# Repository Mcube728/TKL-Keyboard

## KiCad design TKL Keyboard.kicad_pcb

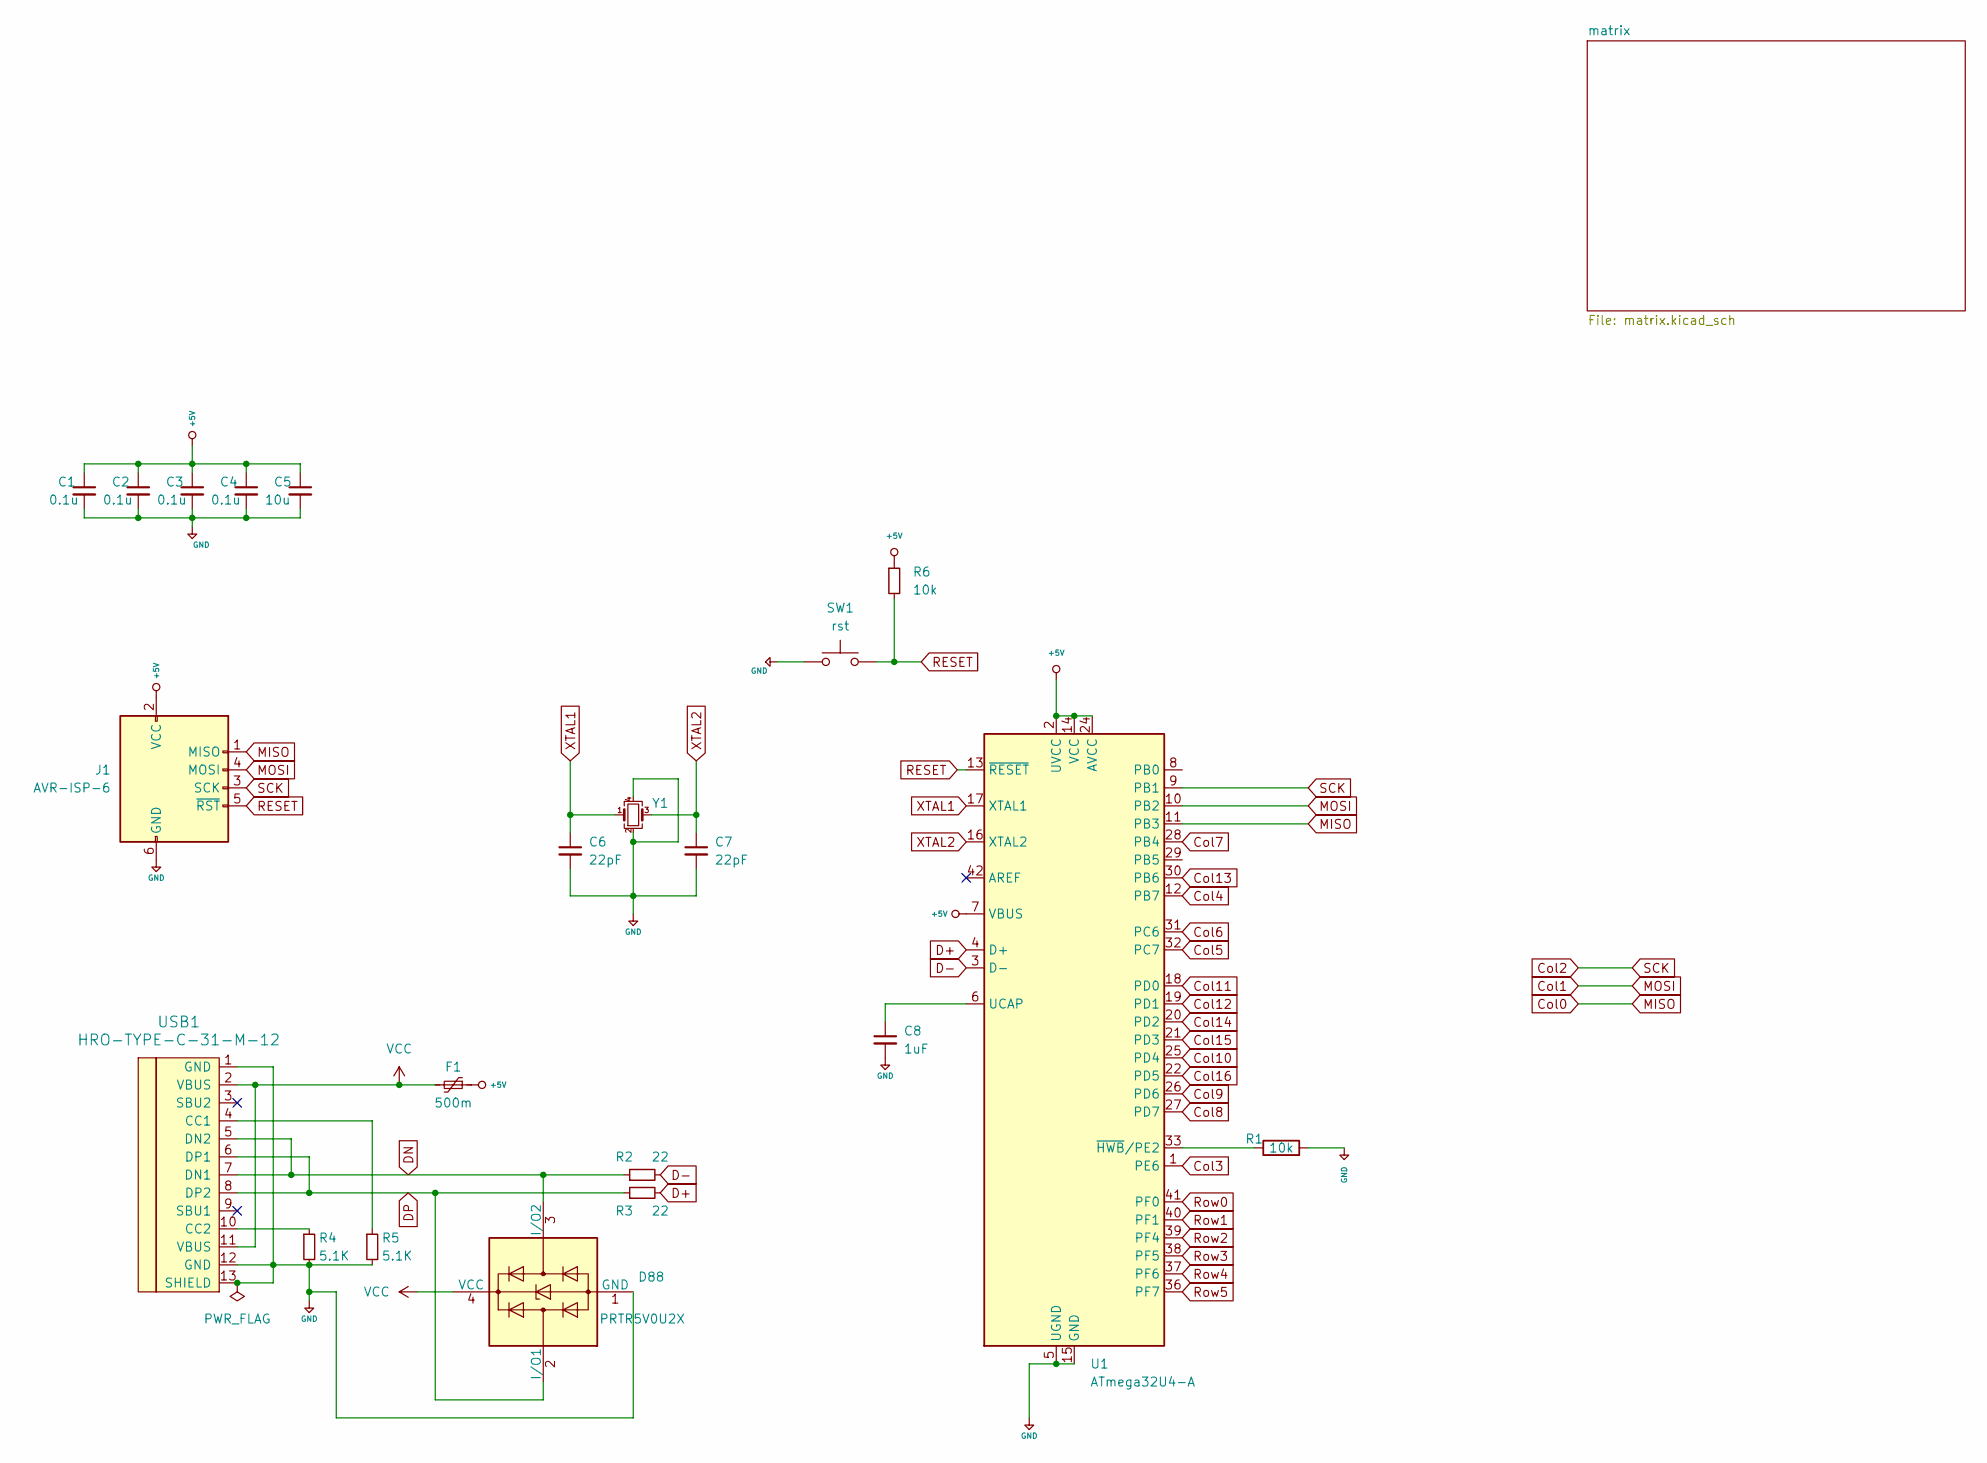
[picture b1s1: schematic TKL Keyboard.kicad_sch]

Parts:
C1, C2, C3, C4: 0.1u; C_0805_2012Metric_Pad1.18x1.45mm_HandSolder
C5: 10u; C_0805_2012Metric_Pad1.18x1.45mm_HandSolder
C6, C7: 22pF; C_0805_2012Metric_Pad1.18x1.45mm_HandSolder
C8: 1uF; C_0805_2012Metric_Pad1.18x1.45mm_HandSolder
D88: PRTR5V0U2X; SOT-143
F1: 500m; Fuse_1206_3216Metric_Pad1.42x1.75mm_HandSolder
J1: AVR-ISP-6; Reset_Pretty-Mask
R1, R6: 10k; R_0805_2012Metric_Pad1.20x1.40mm_HandSolder
R2, R3: 22; R_0805_2012Metric_Pad1.20x1.40mm_HandSolder
R4, R5: 5.1K; R_0805_2012Metric_Pad1.20x1.40mm_HandSolder
SW1: rst; SW_SPST_SKQG_WithStem
U1: ATmega32U4-A; TQFP-44_10x10mm_P0.8mm
USB1: HRO-TYPE-C-31-M-12; HRO-TYPE-C-31-M-12-HandSoldering
Y1: Crystal_SMD_3225-4Pin_3.2x2.5mm_HandSoldering

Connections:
Col0: J1.1 (MISO), U1.11 (PB3); also elsewhere on the board
Col1: J1.4 (MOSI), U1.10 (PB2); also elsewhere on the board
Col2: J1.3 (SCK), U1.9 (PB1); also elsewhere on the board
Col3: U1.1 (PE6); also elsewhere on the board
Col4: U1.12 (PB7); also elsewhere on the board
Col5: U1.32 (PC7); also elsewhere on the board
Col6: U1.31 (PC6); also elsewhere on the board
Col7: U1.28 (PB4); also elsewhere on the board
Col8: U1.27 (PD7); also elsewhere on the board
Col9: U1.26 (PD6); also elsewhere on the board
Col10: U1.25 (PD4); also elsewhere on the board
Col11: U1.18 (PD0); also elsewhere on the board
Col12: U1.19 (PD1); also elsewhere on the board
Col13: U1.30 (PB6); also elsewhere on the board
Col14: U1.20 (PD2); also elsewhere on the board
Col15: U1.21 (PD3); also elsewhere on the board
Col16: U1.22 (PD5); also elsewhere on the board
D+: R3.2, U1.4 (D+)
D-: R2.2, U1.3 (D-)
DN: D88.3 (I/O2), R2.1, USB1.5 (DN2), USB1.7 (DN1)
DP: D88.2 (I/O1), R3.1, USB1.6 (DP1), USB1.8 (DP2)
unnamed: C8.1, U1.6 (UCAP)
unnamed: R1.1, U1.33 (~HWB/PE2)
unnamed: R5.1, USB1.4 (CC1)
unnamed: R4.1, USB1.10 (CC2)
RESET: J1.5 (~RST), R6.2, SW1.2, U1.13 (~RESET)
Row0: U1.41 (PF0); also elsewhere on the board
Row1: U1.40 (PF1); also elsewhere on the board
Row2: U1.39 (PF4); also elsewhere on the board
Row3: U1.38 (PF5); also elsewhere on the board
Row4: U1.37 (PF6); also elsewhere on the board
Row5: U1.36 (PF7); also elsewhere on the board
VCC: D88.4 (VCC), F1.2, USB1.2 (VBUS), USB1.11 (VBUS)
XTAL1: C6.1, U1.17 (XTAL1), Y1.1
XTAL2: C7.1, U1.16 (XTAL2), Y1.3

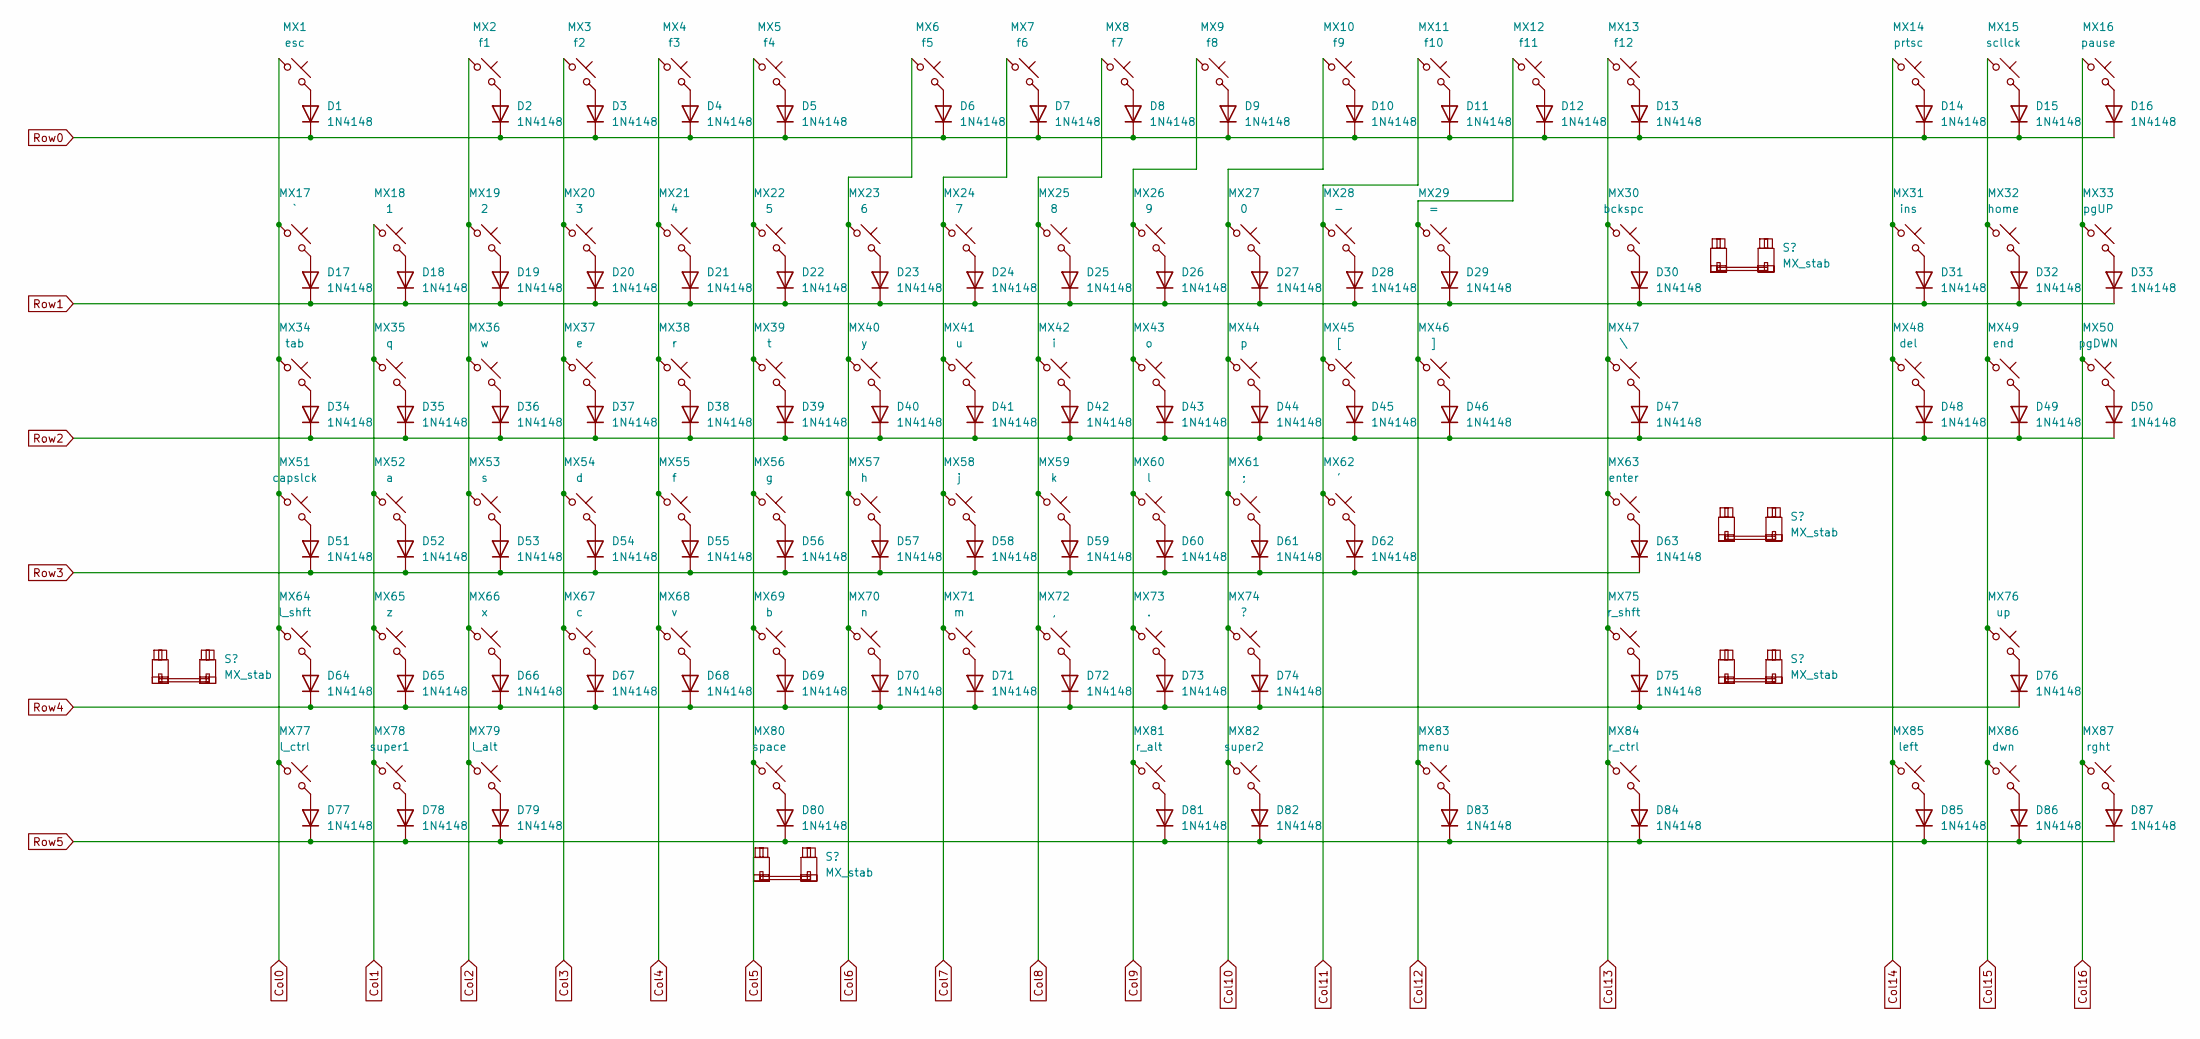
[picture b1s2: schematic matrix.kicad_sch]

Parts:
D1, D2, D3, D4, D5, D6, D7, D8, D9, D10, D11, D12, D13, D14, D15, D16, D17, D18, D19, D20, D21, D22, D23, D24, D25, D26, D27, D28, D29, D30, D31, D32, D33, D34, D35, D36, D37, D38, D39, D40, D41, D42, D43, D44, D45, D46, D47, D48, D49, D50, D51, D52, D53, D54, D55, D56, D57, D58, D59, D60, D61, D62, D63, D64, D65, D66, D67, D68, D69, D70, D71, D72, D73, D74, D75, D76, D77, D78, D79, D80, D81, D82, D83, D84, D85, D86, D87: 1N4148; D_1206_3216Metric_Pad1.42x1.75mm_HandSolder
MX1: esc; SW_MX_1u
MX2: f1; SW_MX_1u
MX3: f2; SW_MX_1u
MX4: f3; SW_MX_1u
MX5: f4; SW_MX_1u
MX6: f5; SW_MX_1u
MX7: f6; SW_MX_1u
MX8: f7; SW_MX_1u
MX9: f8; SW_MX_1u
MX10: f9; SW_MX_1u
MX11: f10; SW_MX_1u
MX12: f11; SW_MX_1u
MX13: f12; SW_MX_1u
MX14: prtsc; SW_MX_1u
MX15: scllck; SW_MX_1u
MX16: pause; SW_MX_1u
MX17: `; SW_MX_1u
MX18: 1; SW_MX_1u
MX19: 2; SW_MX_1u
MX20: 3; SW_MX_1u
MX21: 4; SW_MX_1u
MX22: 5; SW_MX_1u
MX23: 6; SW_MX_1u
MX24: 7; SW_MX_1u
MX25: 8; SW_MX_1u
MX26: 9; SW_MX_1u
MX27: 0; SW_MX_1u
MX28: -; SW_MX_1u
MX29: =; SW_MX_1u
MX30: bckspc; SW_MX_1u
MX31: ins; SW_MX_1u
MX32: home; SW_MX_1u
MX33: pgUP; SW_MX_1u
MX34: tab; SW_MX_1.5u
MX35: q; SW_MX_1u
MX36: w; SW_MX_1u
MX37: e; SW_MX_1u
MX38: r; SW_MX_1u
MX39: t; SW_MX_1u
MX40: y; SW_MX_1u
MX41: u; SW_MX_1u
MX42: i; SW_MX_1u
MX43: o; SW_MX_1u
MX44: p; SW_MX_1u
MX45: [; SW_MX_1u
MX46: ]; SW_MX_1u
MX47: \; SW_MX_1.5u
MX48: del; SW_MX_1u
MX49: end; SW_MX_1u
MX50: pgDWN; SW_MX_1u
MX51: capslck; SW_MX_1.75u
MX52: a; SW_MX_1u
MX53: s; SW_MX_1u
MX54: d; SW_MX_1u
MX55: f; SW_MX_1u
MX56: g; SW_MX_1u
MX57: h; SW_MX_1u
MX58: j; SW_MX_1u
MX59: k; SW_MX_1u
MX60: l; SW_MX_1u
MX61: ;; SW_MX_1u
MX62: '; SW_MX_1u
MX63: enter; SW_MX_1u
MX64: l_shft; SW_MX_1u
MX65: z; SW_MX_1u
MX66: x; SW_MX_1u
MX67: c; SW_MX_1u
MX68: v; SW_MX_1u
MX69: b; SW_MX_1u
MX70: n; SW_MX_1u
MX71: m; SW_MX_1u
MX72: ,; SW_MX_1u
MX73: .; SW_MX_1u
MX74: ?; SW_MX_1u
MX75: r_shft; SW_MX_1u
MX76: up; SW_MX_1u
MX77: l_ctrl; SW_MX_1.25u
MX78: super1; SW_MX_1.25u
MX79: l_alt; SW_MX_1.25u
MX80: space; SW_MX_1u
MX81: r_alt; SW_MX_1.25u
MX82: super2; SW_MX_1.25u
MX83: menu; SW_MX_1.25u
MX84: r_ctrl; SW_MX_1.25u
MX85: left; SW_MX_1u
MX86: dwn; SW_MX_1u
MX87: rght; SW_MX_1u
S1: MX_stab; STAB_MX_P_2u
S2, S3: MX_stab; STAB_MX_P_2.25u
S4: MX_stab; STAB_MX_P_2.75u
S5: MX_stab; STAB_MX_P_6.25u

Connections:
Col0: MX1.1, MX17.1, MX34.1, MX51.1, MX64.1, MX77.1; also elsewhere on the board
Col1: MX18.1, MX35.1, MX52.1, MX65.1, MX78.1; also elsewhere on the board
Col2: MX2.1, MX19.1, MX36.1, MX53.1, MX66.1, MX79.1; also elsewhere on the board
Col3: MX3.1, MX20.1, MX37.1, MX54.1, MX67.1; also elsewhere on the board
Col4: MX4.1, MX21.1, MX38.1, MX55.1, MX68.1; also elsewhere on the board
Col5: MX5.1, MX22.1, MX39.1, MX56.1, MX69.1, MX80.1; also elsewhere on the board
Col6: MX6.1, MX23.1, MX40.1, MX57.1, MX70.1; also elsewhere on the board
Col7: MX7.1, MX24.1, MX41.1, MX58.1, MX71.1; also elsewhere on the board
Col8: MX8.1, MX25.1, MX42.1, MX59.1, MX72.1; also elsewhere on the board
Col9: MX9.1, MX26.1, MX43.1, MX60.1, MX73.1, MX81.1; also elsewhere on the board
Col10: MX10.1, MX27.1, MX44.1, MX61.1, MX74.1, MX82.1; also elsewhere on the board
Col11: MX11.1, MX28.1, MX45.1, MX62.1; also elsewhere on the board
Col12: MX12.1, MX29.1, MX46.1, MX83.1; also elsewhere on the board
Col13: MX13.1, MX30.1, MX47.1, MX63.1, MX75.1, MX84.1; also elsewhere on the board
Col14: MX14.1, MX31.1, MX48.1, MX85.1; also elsewhere on the board
Col15: MX15.1, MX32.1, MX49.1, MX76.1, MX86.1; also elsewhere on the board
Col16: MX16.1, MX33.1, MX50.1, MX87.1; also elsewhere on the board
unnamed: D1.2 (A), MX1.2
unnamed: D2.2 (A), MX2.2
unnamed: D3.2 (A), MX3.2
unnamed: D4.2 (A), MX4.2
unnamed: D5.2 (A), MX5.2
unnamed: D6.2 (A), MX6.2
unnamed: D7.2 (A), MX7.2
unnamed: D8.2 (A), MX8.2
unnamed: D9.2 (A), MX9.2
unnamed: D10.2 (A), MX10.2
unnamed: D11.2 (A), MX11.2
unnamed: D12.2 (A), MX12.2
unnamed: D13.2 (A), MX13.2
unnamed: D14.2 (A), MX14.2
unnamed: D15.2 (A), MX15.2
unnamed: D16.2 (A), MX16.2
unnamed: D17.2 (A), MX17.2
unnamed: D18.2 (A), MX18.2
unnamed: D19.2 (A), MX19.2
unnamed: D20.2 (A), MX20.2
unnamed: D21.2 (A), MX21.2
unnamed: D22.2 (A), MX22.2
unnamed: D23.2 (A), MX23.2
unnamed: D24.2 (A), MX24.2
unnamed: D25.2 (A), MX25.2
unnamed: D26.2 (A), MX26.2
unnamed: D27.2 (A), MX27.2
unnamed: D28.2 (A), MX28.2
unnamed: D29.2 (A), MX29.2
unnamed: D30.2 (A), MX30.2
unnamed: D31.2 (A), MX31.2
unnamed: D32.2 (A), MX32.2
unnamed: D33.2 (A), MX33.2
unnamed: D34.2 (A), MX34.2
unnamed: D35.2 (A), MX35.2
unnamed: D36.2 (A), MX36.2
unnamed: D37.2 (A), MX37.2
unnamed: D38.2 (A), MX38.2
unnamed: D39.2 (A), MX39.2
unnamed: D40.2 (A), MX40.2
unnamed: D41.2 (A), MX41.2
unnamed: D42.2 (A), MX42.2
unnamed: D43.2 (A), MX43.2
unnamed: D44.2 (A), MX44.2
unnamed: D45.2 (A), MX45.2
unnamed: D46.2 (A), MX46.2
unnamed: D47.2 (A), MX47.2
unnamed: D48.2 (A), MX48.2
unnamed: D49.2 (A), MX49.2
unnamed: D50.2 (A), MX50.2
unnamed: D51.2 (A), MX51.2
unnamed: D52.2 (A), MX52.2
unnamed: D53.2 (A), MX53.2
unnamed: D54.2 (A), MX54.2
unnamed: D55.2 (A), MX55.2
unnamed: D56.2 (A), MX56.2
unnamed: D57.2 (A), MX57.2
unnamed: D58.2 (A), MX58.2
unnamed: D59.2 (A), MX59.2
unnamed: D60.2 (A), MX60.2
unnamed: D61.2 (A), MX61.2
unnamed: D62.2 (A), MX62.2
unnamed: D63.2 (A), MX63.2
unnamed: D64.2 (A), MX64.2
unnamed: D65.2 (A), MX65.2
unnamed: D66.2 (A), MX66.2
unnamed: D67.2 (A), MX67.2
unnamed: D68.2 (A), MX68.2
unnamed: D69.2 (A), MX69.2
unnamed: D70.2 (A), MX70.2
unnamed: D71.2 (A), MX71.2
unnamed: D72.2 (A), MX72.2
unnamed: D73.2 (A), MX73.2
unnamed: D74.2 (A), MX74.2
unnamed: D75.2 (A), MX75.2
unnamed: D76.2 (A), MX76.2
unnamed: D77.2 (A), MX77.2
unnamed: D78.2 (A), MX78.2
unnamed: D79.2 (A), MX79.2
unnamed: D80.2 (A), MX80.2
unnamed: D81.2 (A), MX81.2
unnamed: D82.2 (A), MX82.2
unnamed: D83.2 (A), MX83.2
unnamed: D84.2 (A), MX84.2
unnamed: D85.2 (A), MX85.2
unnamed: D86.2 (A), MX86.2
unnamed: D87.2 (A), MX87.2
Row0: D1.1 (K), D2.1 (K), D3.1 (K), D4.1 (K), D5.1 (K), D6.1 (K), D7.1 (K), D8.1 (K), D9.1 (K), D10.1 (K), D11.1 (K), D12.1 (K), D13.1 (K), D14.1 (K), D15.1 (K), D16.1 (K); also elsewhere on the board
Row1: D17.1 (K), D18.1 (K), D19.1 (K), D20.1 (K), D21.1 (K), D22.1 (K), D23.1 (K), D24.1 (K), D25.1 (K), D26.1 (K), D27.1 (K), D28.1 (K), D29.1 (K), D30.1 (K), D31.1 (K), D32.1 (K), D33.1 (K); also elsewhere on the board
Row2: D34.1 (K), D35.1 (K), D36.1 (K), D37.1 (K), D38.1 (K), D39.1 (K), D40.1 (K), D41.1 (K), D42.1 (K), D43.1 (K), D44.1 (K), D45.1 (K), D46.1 (K), D47.1 (K), D48.1 (K), D49.1 (K), D50.1 (K); also elsewhere on the board
Row3: D51.1 (K), D52.1 (K), D53.1 (K), D54.1 (K), D55.1 (K), D56.1 (K), D57.1 (K), D58.1 (K), D59.1 (K), D60.1 (K), D61.1 (K), D62.1 (K), D63.1 (K); also elsewhere on the board
Row4: D64.1 (K), D65.1 (K), D66.1 (K), D67.1 (K), D68.1 (K), D69.1 (K), D70.1 (K), D71.1 (K), D72.1 (K), D73.1 (K), D74.1 (K), D75.1 (K), D76.1 (K); also elsewhere on the board
Row5: D77.1 (K), D78.1 (K), D79.1 (K), D80.1 (K), D81.1 (K), D82.1 (K), D83.1 (K), D84.1 (K), D85.1 (K), D86.1 (K), D87.1 (K); also elsewhere on the board

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
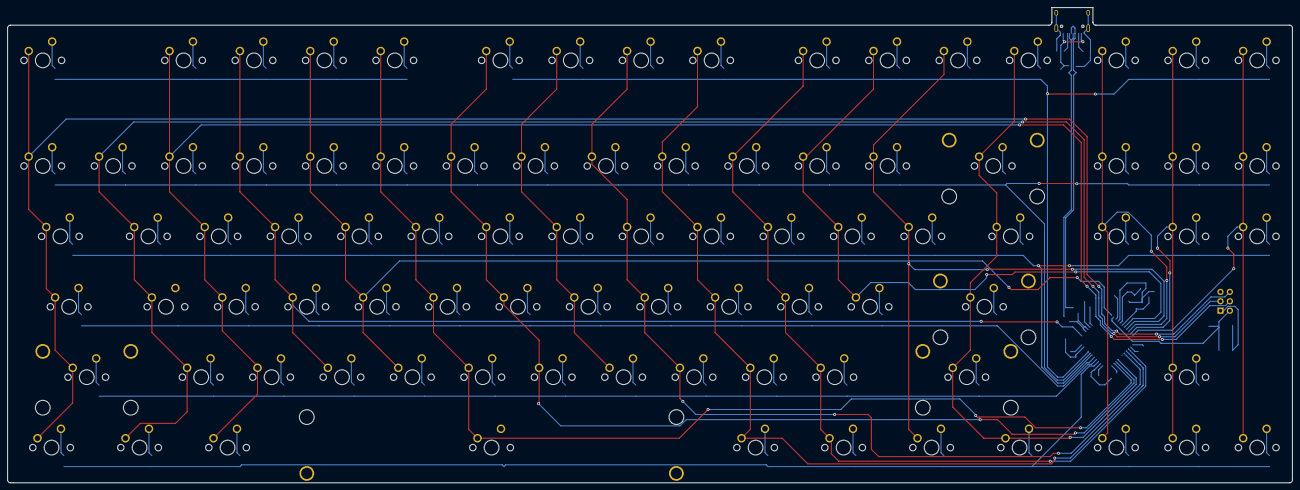
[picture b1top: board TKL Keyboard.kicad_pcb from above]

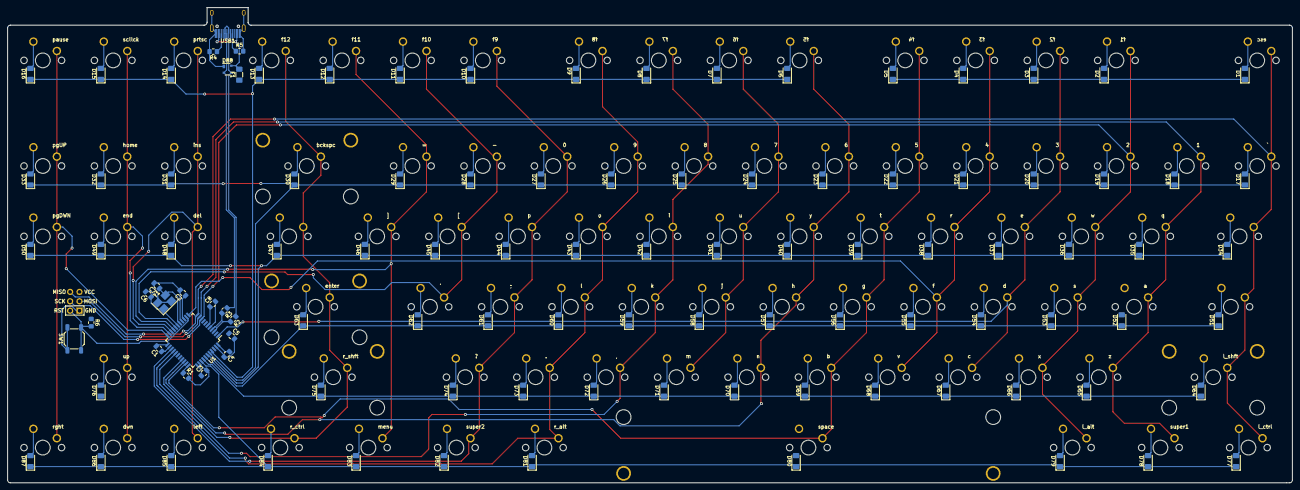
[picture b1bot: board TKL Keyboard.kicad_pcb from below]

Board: 2 copper layers, 347.7 x 128.6 mm, 200 parts (108 on the bottom side), 123 nets.
